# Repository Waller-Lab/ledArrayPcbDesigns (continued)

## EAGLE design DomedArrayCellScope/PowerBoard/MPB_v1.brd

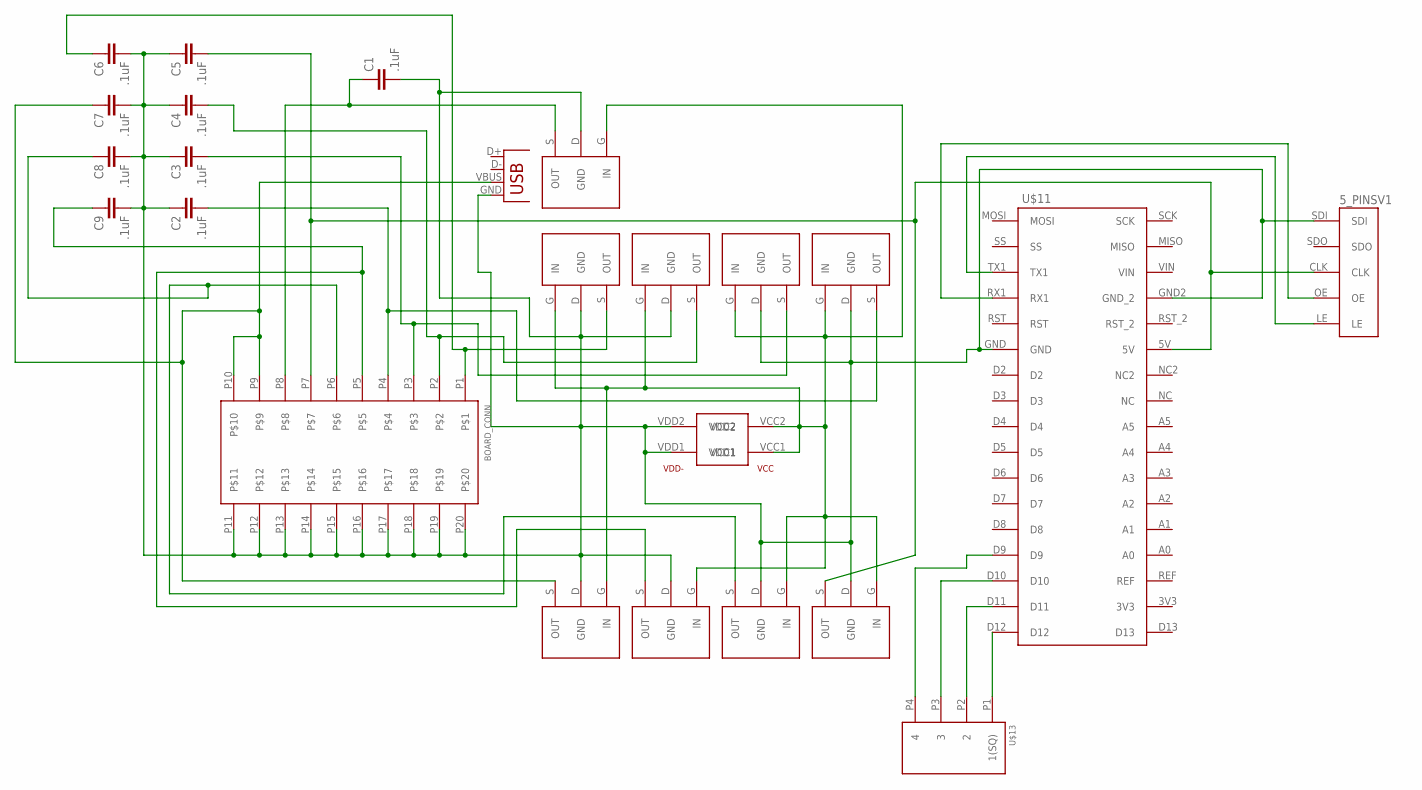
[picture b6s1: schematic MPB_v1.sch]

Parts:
BOARD_CONN: 20PIN_HEADER; 20PIN_3MMHEADER
C1, C2, C3, C4, C5, C6, C7, C8, C9: .1uF; CAP-PTH-SMALL-KIT
PWR: 4PIN_POWER; KPJX-4S
R1, R2, R3, R4, R5, R6, R7, R8, R9: 5VREG; TO220BH
U$11: ARDUINOMICRO1; ARDUINOMICRO
U$12: 5_PINSV1; 5PIN_HOLES
U$13: 4_PINS1; 4PIN_HOLES
_: USB-A-SMD; USB-A-S-NOSILK-FEMALE

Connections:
unnamed: PWR.VCC1, PWR.VCC2, R1.G (IN), R2.G (IN), R3.G (IN), R4.G (IN), R5.G (IN), R6.G (IN), R7.G (IN), R8.G (IN), R9.G (IN)
unnamed: BOARD_CONN.P1, C6.1, R9.S (OUT)
unnamed: BOARD_CONN.P2, C4.2, R1.S (OUT)
unnamed: U$11.TX1, U$12.LE
unnamed: BOARD_CONN.P3, C3.2, R3.S (OUT)
unnamed: BOARD_CONN.P4, C2.2, R2.S (OUT)
unnamed: BOARD_CONN.P11, BOARD_CONN.P12, BOARD_CONN.P13, BOARD_CONN.P14, BOARD_CONN.P15, BOARD_CONN.P16, BOARD_CONN.P17, BOARD_CONN.P18, BOARD_CONN.P19, BOARD_CONN.P20, C1.2, C2.1, C3.1, C4.1, C5.1, C6.2, C7.2, C8.2, C9.2, PWR.VDD1, PWR.VDD2, R1.D (GND), R2.D (GND), R3.D (GND), R4.D (GND), R5.D (GND), R6.D (GND), R7.D (GND), R8.D (GND), R9.D (GND), U$11.GND, U$11.GND2 (GND_2), U$12.SDI, _.GND
unnamed: BOARD_CONN.P9, BOARD_CONN.P10, C7.1, R5.S (OUT), _.VBUS
unnamed: U$11.D12, U$13.P1 (1(SQ))
unnamed: BOARD_CONN.P5, C9.1, R6.S (OUT)
unnamed: BOARD_CONN.P6, C8.1, R8.S (OUT)
unnamed: BOARD_CONN.P7, C5.2, R4.S (OUT), U$11.5V, U$12.CLK
unnamed: U$11.D11, U$13.P2 (2)
unnamed: U$11.D10, U$13.P3 (3)
unnamed: U$11.D9, U$13.P4 (4)
unnamed: U$11.RX1, U$12.OE
unnamed: BOARD_CONN.P8, C1.1, R7.S (OUT)

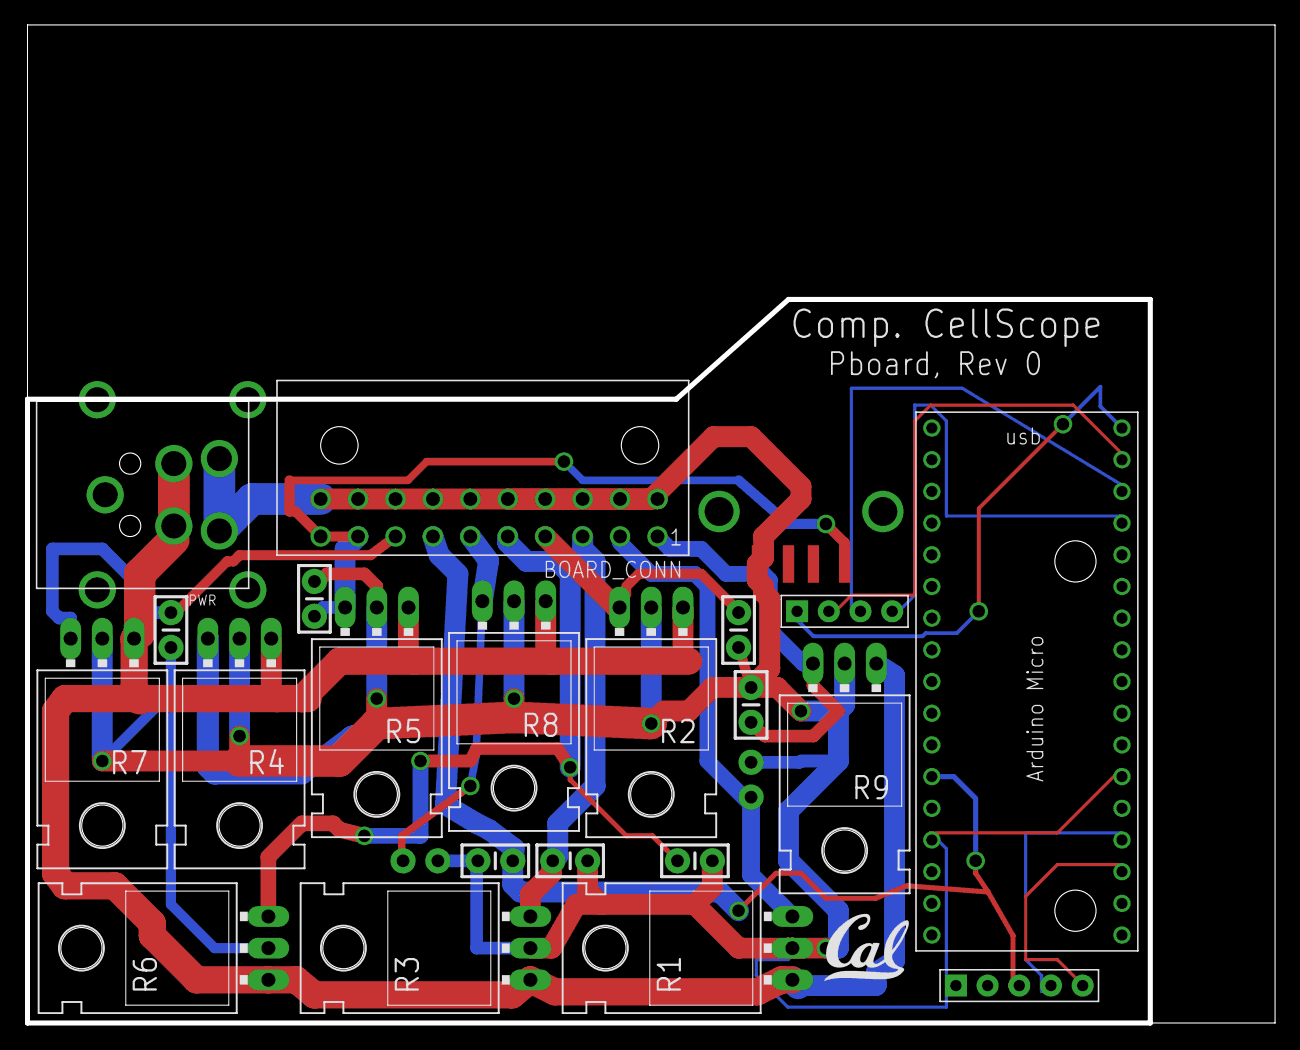
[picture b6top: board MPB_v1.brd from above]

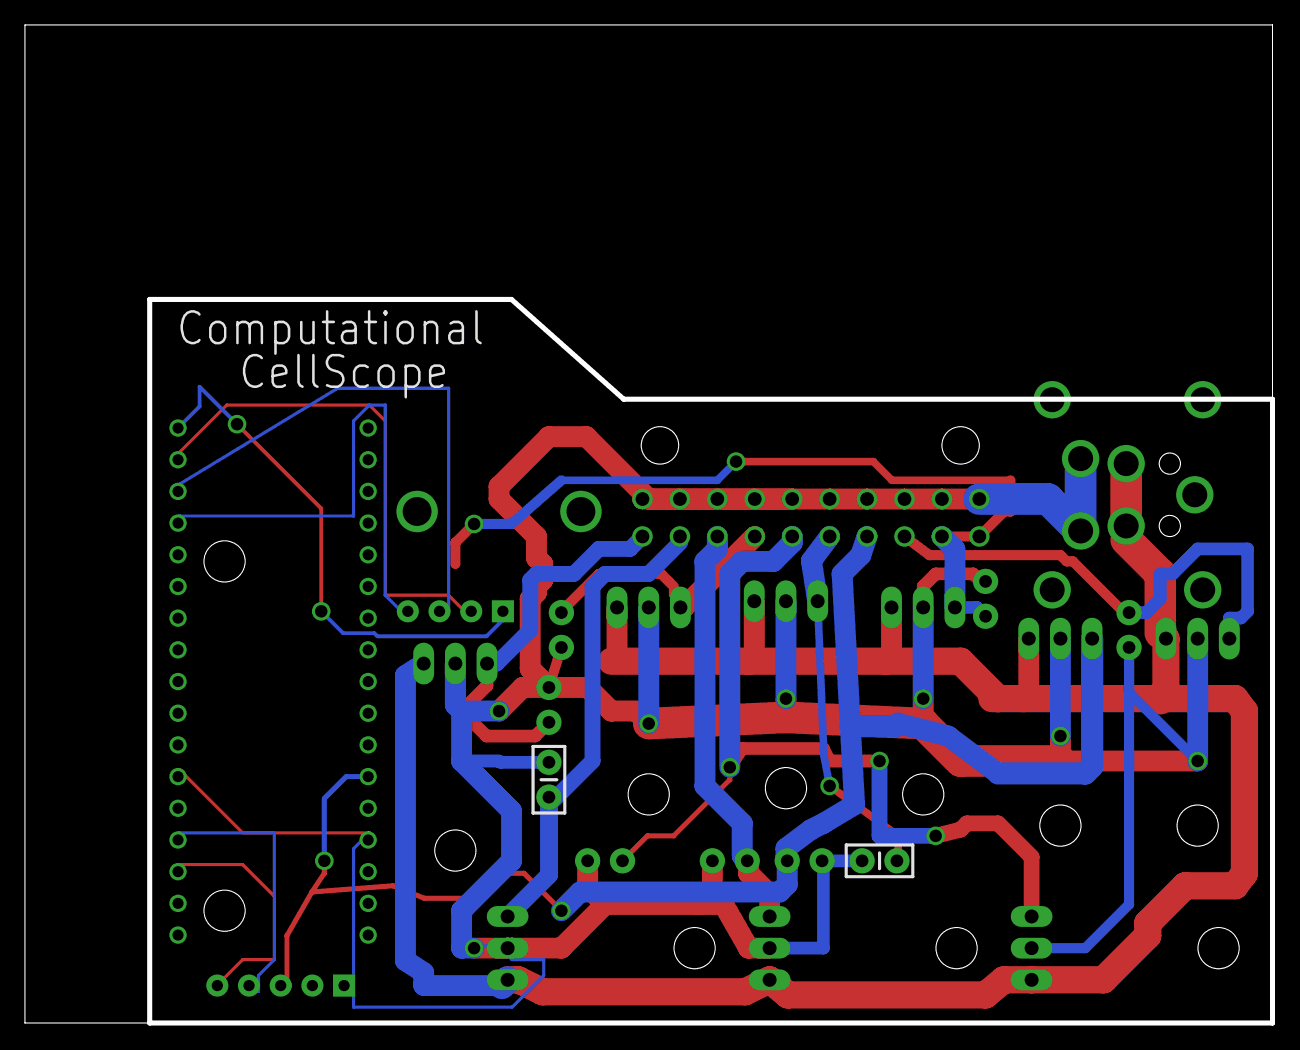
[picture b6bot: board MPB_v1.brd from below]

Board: 2 copper layers, 100.0 x 80.0 mm, 24 parts (2 on the bottom side), 17 nets.

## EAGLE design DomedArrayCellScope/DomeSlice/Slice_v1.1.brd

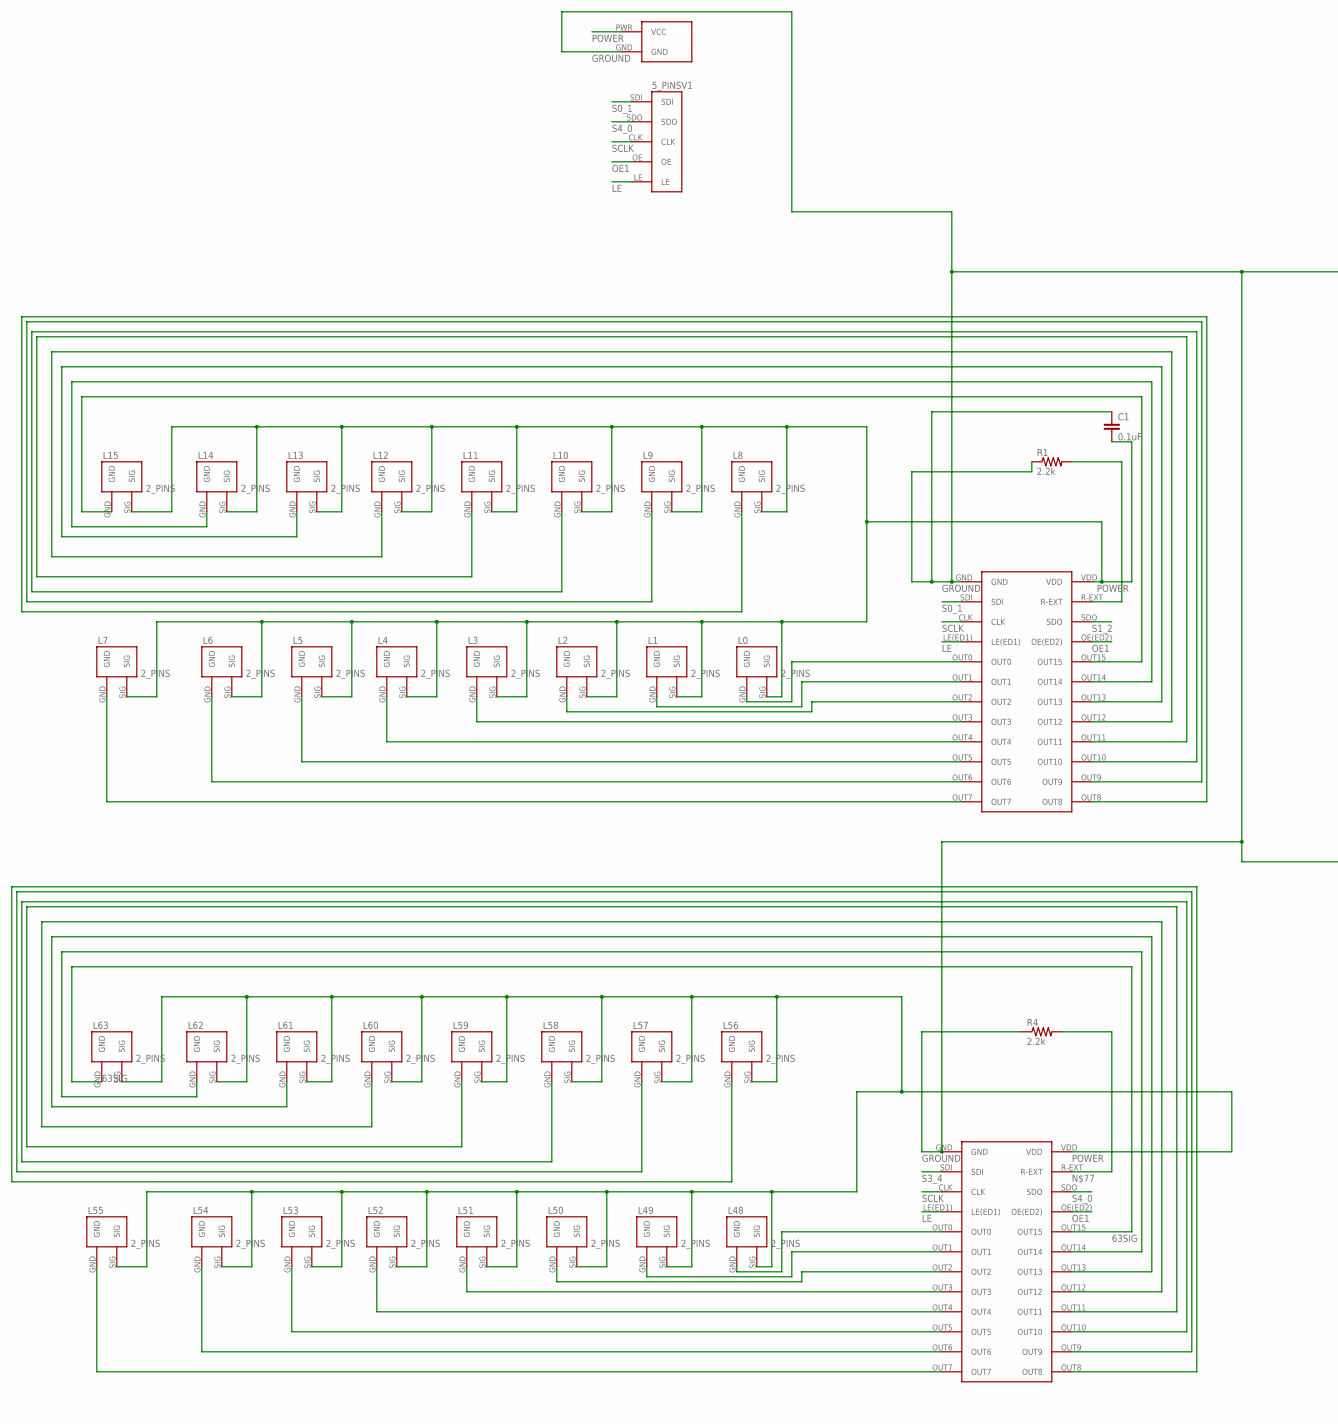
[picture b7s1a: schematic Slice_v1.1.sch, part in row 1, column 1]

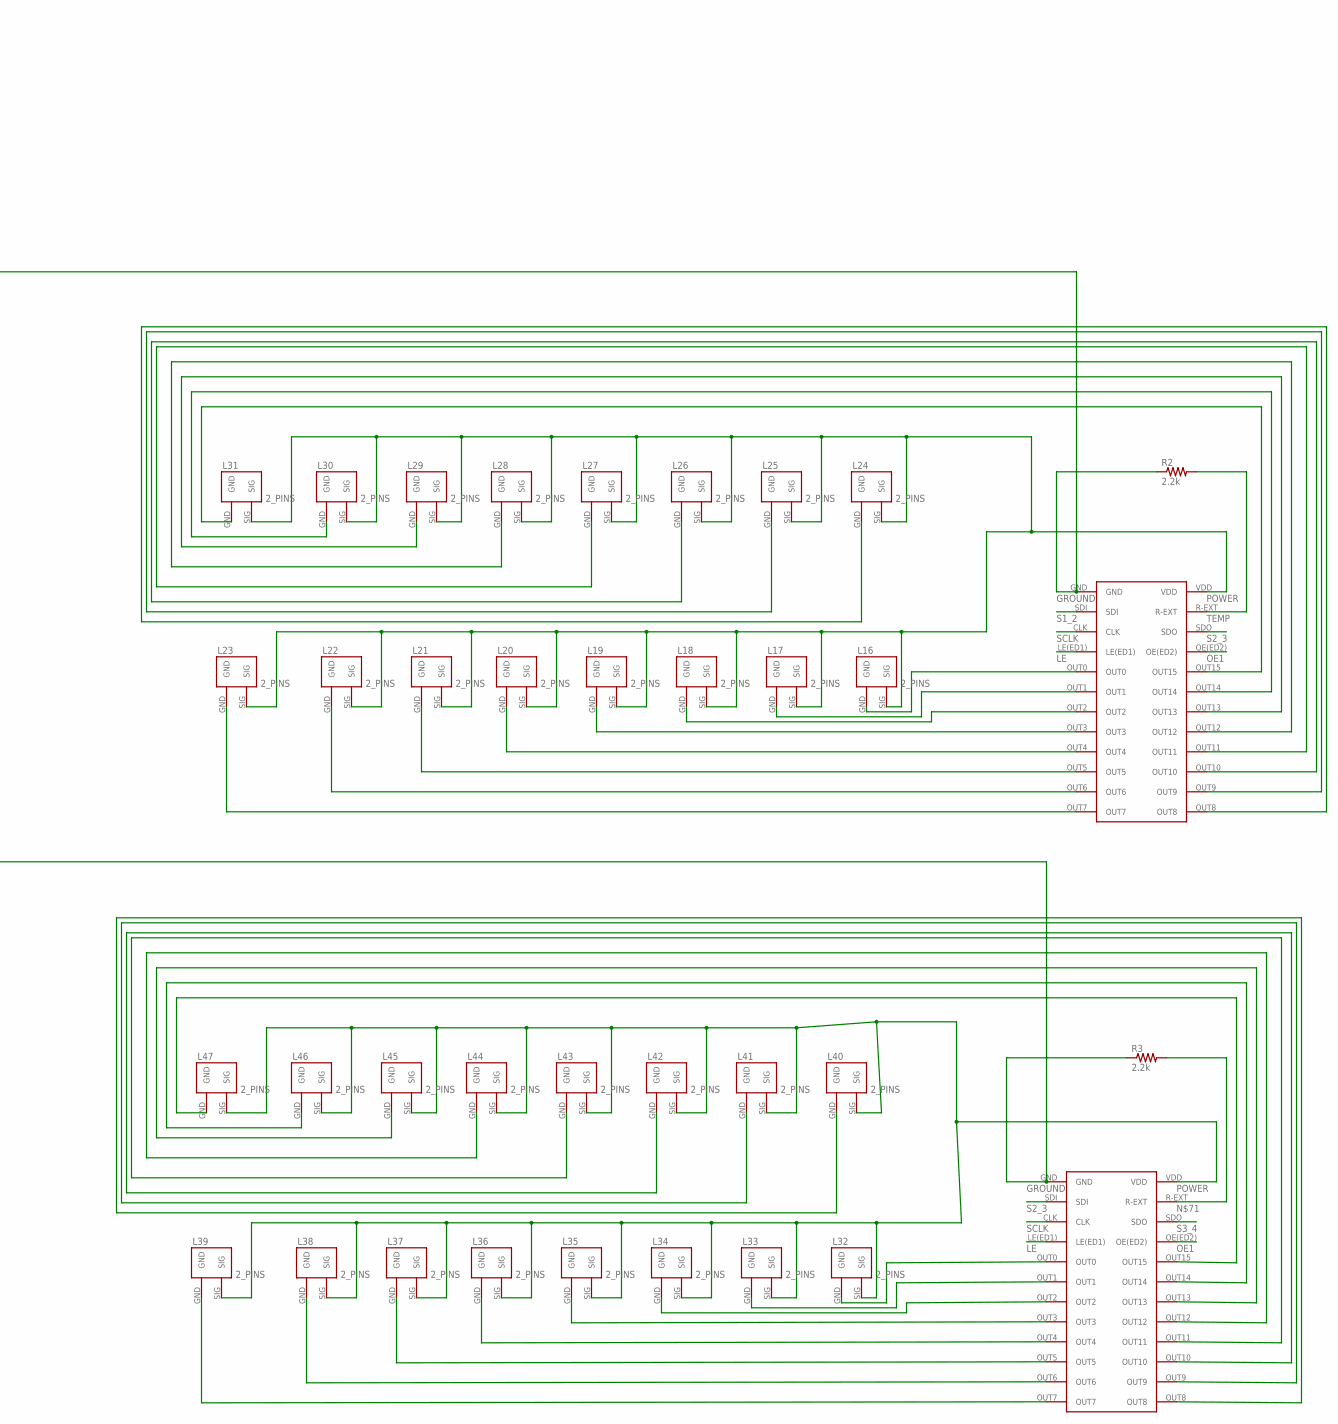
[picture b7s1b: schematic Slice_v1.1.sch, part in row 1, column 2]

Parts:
C1: 0.1uF; 0603-CAP
L0, L1, L2, L3, L4, L5, L6, L7, L8, L9, L10, L11, L12, L13, L14, L15, L16, L17, L18, L19, L20, L21, L22, L23, L24, L25, L26, L27, L28, L29, L30, L31, L32, L33, L34, L35, L36, L37, L38, L39, L40, L41, L42, L43, L44, L45, L46, L47, L48, L49, L50, L51, L52, L53, L54, L55, L56, L57, L58, L59, L60, L61, L62, L63: 2_PINS; 2PIN_HOLES
R1, R2, R3, R4: 2.2k; AXIAL-0.3EZ
U$1, U$2, U$3, U$4: TLC5926
U$6: 2PIN_2ATE; TE_A32471
U$7: 5_PINSV1; 5PIN_HOLES

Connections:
63SIG: L63.GND, U$2.OUT15
GROUND: C1.1, R1.P$1 (1), R2.P$1 (1), R3.P$1 (1), R4.P$1 (1), U$1.GND, U$2.GND, U$3.GND, U$4.GND, U$6.GND
GSCL: L31.GND, U$4.OUT15
LE: U$1.LE(ED1), U$2.LE(ED1), U$3.LE(ED1), U$4.LE(ED1), U$7.LE
unnamed: L7.GND, U$1.OUT7
unnamed: L6.GND, U$1.OUT6
unnamed: L5.GND, U$1.OUT5
unnamed: L4.GND, U$1.OUT4
unnamed: L3.GND, U$1.OUT3
unnamed: L2.GND, U$1.OUT2
unnamed: L1.GND, U$1.OUT1
unnamed: L0.GND, U$1.OUT0
unnamed: L15.GND, U$1.OUT15
unnamed: L14.GND, U$1.OUT14
unnamed: L13.GND, U$1.OUT13
unnamed: L12.GND, U$1.OUT12
unnamed: L11.GND, U$1.OUT11
unnamed: L10.GND, U$1.OUT10
unnamed: L9.GND, U$1.OUT9
unnamed: L8.GND, U$1.OUT8
unnamed: L23.GND, U$4.OUT7
unnamed: L22.GND, U$4.OUT6
unnamed: L21.GND, U$4.OUT5
unnamed: L20.GND, U$4.OUT4
unnamed: L19.GND, U$4.OUT3
unnamed: L18.GND, U$4.OUT2
unnamed: L17.GND, U$4.OUT1
unnamed: L16.GND, U$4.OUT0
unnamed: L30.GND, U$4.OUT14
unnamed: L29.GND, U$4.OUT13
unnamed: L28.GND, U$4.OUT12
unnamed: L27.GND, U$4.OUT11
unnamed: L26.GND, U$4.OUT10
unnamed: L25.GND, U$4.OUT9
unnamed: L24.GND, U$4.OUT8
unnamed: L55.GND, U$2.OUT7
unnamed: L54.GND, U$2.OUT6
unnamed: L53.GND, U$2.OUT5
unnamed: L52.GND, U$2.OUT4
unnamed: L51.GND, U$2.OUT3
unnamed: L50.GND, U$2.OUT2
unnamed: L49.GND, U$2.OUT1
unnamed: L48.GND, U$2.OUT0
unnamed: L62.GND, U$2.OUT14
unnamed: L61.GND, U$2.OUT13
unnamed: L60.GND, U$2.OUT12
unnamed: L59.GND, U$2.OUT11
unnamed: L58.GND, U$2.OUT10
unnamed: L57.GND, U$2.OUT9
unnamed: L56.GND, U$2.OUT8
unnamed: L39.GND, U$3.OUT7
unnamed: L38.GND, U$3.OUT6
unnamed: L37.GND, U$3.OUT5
unnamed: L36.GND, U$3.OUT4
unnamed: L35.GND, U$3.OUT3
unnamed: L34.GND, U$3.OUT2
unnamed: L33.GND, U$3.OUT1
unnamed: L32.GND, U$3.OUT0
unnamed: L46.GND, U$3.OUT14
unnamed: L45.GND, U$3.OUT13
unnamed: L44.GND, U$3.OUT12
unnamed: L43.GND, U$3.OUT11
unnamed: L42.GND, U$3.OUT10
unnamed: L41.GND, U$3.OUT9
unnamed: L40.GND, U$3.OUT8
unnamed: R1.P$2 (2), U$1.R-EXT
unnamed: R3.P$2 (2), U$3.R-EXT
unnamed: R4.P$2 (2), U$2.R-EXT
OE1: U$1.OE(ED2), U$2.OE(ED2), U$3.OE(ED2), U$4.OE(ED2), U$7.OE
POWER: C1.2, L0.SIG, L1.SIG, L2.SIG, L3.SIG, L4.SIG, L5.SIG, L6.SIG, L7.SIG, L8.SIG, L9.SIG, L10.SIG, L11.SIG, L12.SIG, L13.SIG, L14.SIG, L15.SIG, L16.SIG, L17.SIG, L18.SIG, L19.SIG, L20.SIG, L21.SIG, L22.SIG, L23.SIG, L24.SIG, L25.SIG, L26.SIG, L27.SIG, L28.SIG, L29.SIG, L30.SIG, L31.SIG, L32.SIG, L33.SIG, L34.SIG, L35.SIG, L36.SIG, L37.SIG, L38.SIG, L39.SIG, L40.SIG, L41.SIG, L42.SIG, L43.SIG, L44.SIG, L45.SIG, L46.SIG, L47.SIG, L48.SIG, L49.SIG, L50.SIG, L51.SIG, L52.SIG, L53.SIG, L54.SIG, L55.SIG, L56.SIG, L57.SIG, L58.SIG, L59.SIG, L60.SIG, L61.SIG, L62.SIG, L63.SIG, U$1.VDD, U$2.VDD, U$3.VDD, U$4.VDD, U$6.PWR (VCC)
S0_1: U$1.SDI, U$7.SDI
S1_2: U$1.SDO, U$4.SDI
S2_3: U$3.SDI, U$4.SDO
S3_4: U$2.SDI, U$3.SDO
S4_0: U$2.SDO, U$7.SDO
SCLK: U$1.CLK, U$2.CLK, U$3.CLK, U$4.CLK, U$7.CLK
SOUT: L47.GND, U$3.OUT15
TEMP: R2.P$2 (2), U$4.R-EXT

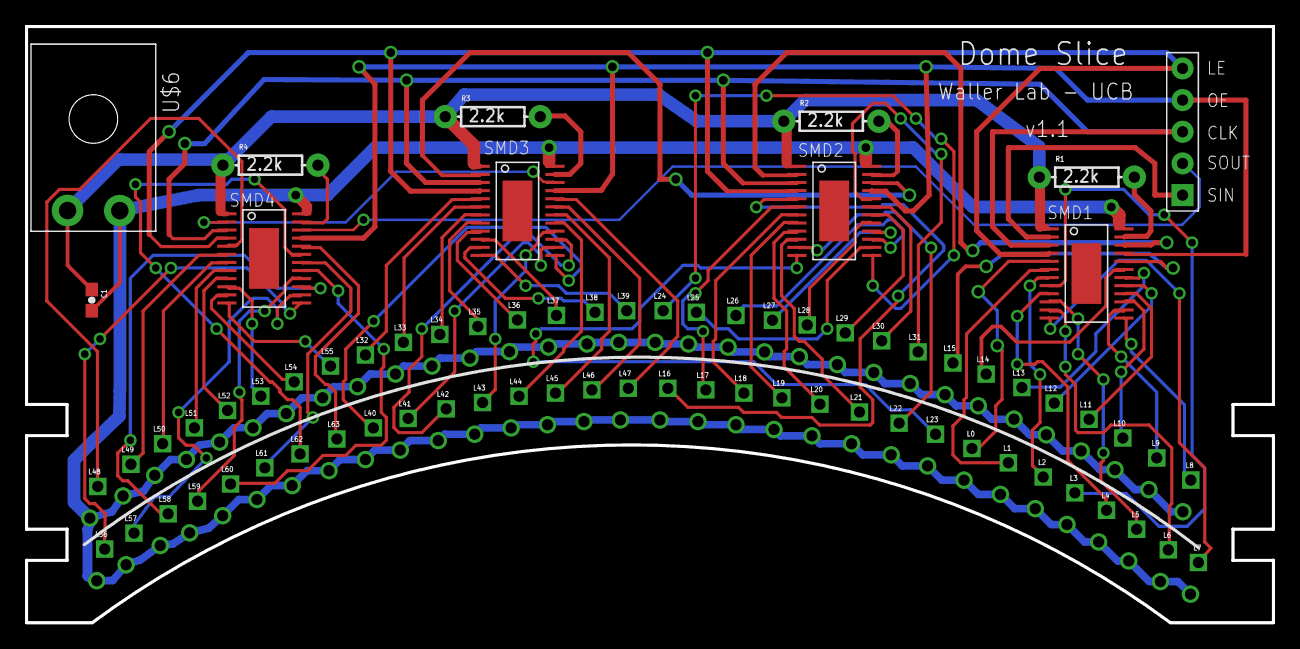
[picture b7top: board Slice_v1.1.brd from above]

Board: 2 copper layers, 100.0 x 47.8 mm, 75 parts (0 on the bottom side), 78 nets.

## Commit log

2015-11-11 Added Existing PCB Designs and Library
    Initial Commit
2015-11-17 Cleaned Up EAGLE Library
2015-11-18 redid schematic for ArchedArray and modified LED part
2015-11-18 Added 28-pin header for TLC5955 breakout
2015-11-19 Finished TLC5955 initial board
2015-11-19 Updated TLC5955 Breakout
    Made 1” in size
2015-11-19 Updated .gitignore for eagle files we don't care about
2015-11-20 TLC Breakout added cap, having trouble with crossed airwires
2015-11-20 Updated TLC board, added .lck files to gitignore
2015-11-20 Fixed TLC5955 right side
2015-11-21 Small trace changes on TI5955 for more compact traces.
2015-12-01 added slice_v7 ArchedArray with 4 layers
2015-12-08 ArchedArray before moving board 6
2015-12-23 finished wiring Arched Array
2015-12-27 added changes to ArchedArray board according to email
2016-01-07 Added Latest Planar Array CAD Files
2016-01-07 Updated .gitignore
2016-01-07 made new folder for DomedArray and made dimension changes to pcb with new hole diameters and edges
2016-01-15 Updated Planar Array Designs
2016-01-19 Planar Array partial route
2016-01-27 new 4P X 8S device and updated DomedArray board
2016-01-28 Added Eagle Flange Base Placement Macro and output
2016-01-28 Updated Script
2016-01-28 Another Update for board placement macro
2016-01-28 Updated Dome PCB layout dimensions
2016-02-02 dome board2 board routed
